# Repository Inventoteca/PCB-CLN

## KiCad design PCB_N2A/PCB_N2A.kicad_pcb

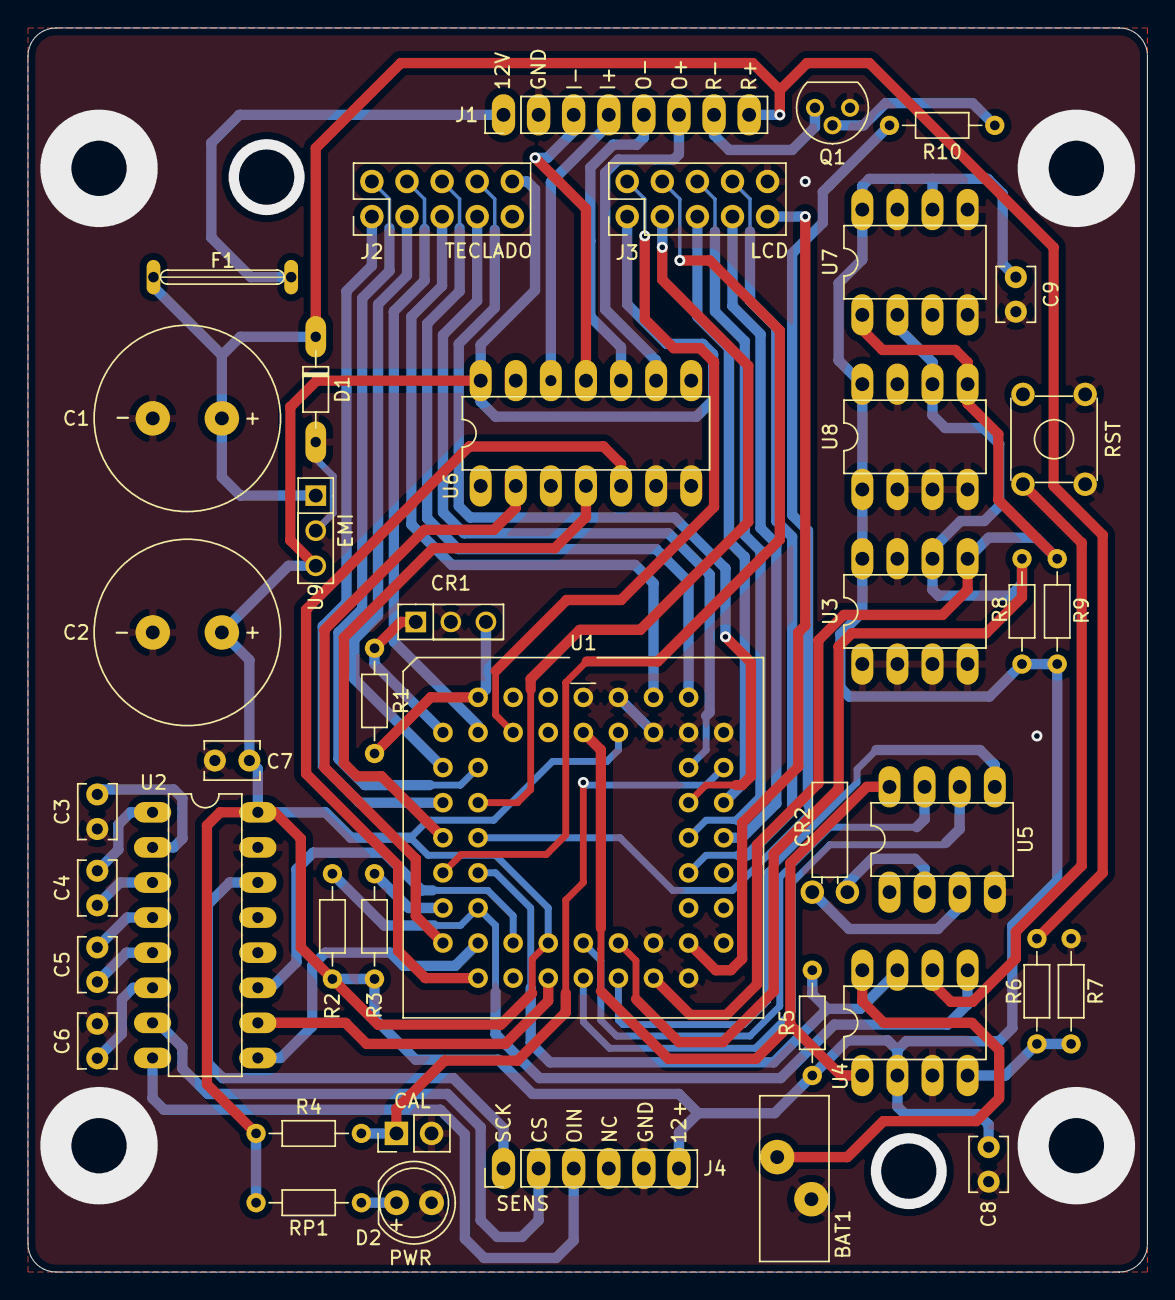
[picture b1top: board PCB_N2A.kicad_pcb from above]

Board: 2 copper layers, 81.0 x 90.0 mm, 42 parts (0 on the bottom side), 59 nets.

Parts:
BAT1: Battery_Cell; BatteryHolder_5.5_5mm
C1, C2: CP_Small; CP_13.25_5.0mm
C3, C4, C5, C6, C7, C8, C9: C_Small; C_Disc_D3.8mm_W2.6mm_P2.50mm
CAL: Conn_01x02; PinHeader_1x02_P2.54mm_Vertical
CR1: Crystal_GND2; Crystal_PIN-3
CR2: Crystal; crystal_2.54_8.7mm
D1: DIODE; D_DO-34_SOD68_P7.62mm_Horizontal
D2: RED; LED_D5.0mm_IRBlack
F1: Fuse; FUSE_10mm
J1: Conn_01x08; PinHeader_1x08_P2.54mm_Vertical
J2: Teclado; PinHeader_2x05_P2.54mm_Vertical
J3: LCD; PinHeader_2x05_P2.54mm_Vertical
J4: SENS; PinHeader_1x06_P2.54mm_Vertical
Q1: BC547; TO-92
R1: 10M; R_Axial_DIN0204_L3.6mm_D1.6mm_P7.62mm_Horizontal
R2, R3, R4, R5, R6, R8, R9, R10: 9.1k; R_Axial_DIN0204_L3.6mm_D1.6mm_P7.62mm_Horizontal
R7: 3.3k; R_Axial_DIN0204_L3.6mm_D1.6mm_P7.62mm_Horizontal
RP1: 360; R_Axial_DIN0204_L3.6mm_D1.6mm_P7.62mm_Horizontal
RST1: SW_Push_Dual; SW_TH_Tactile_Omron_B3F-10xx
U1: 68HC11_PLCC; PLCC-52_THT-Socket
U2: MAX232CPE; DIP-16_W7.62mm
U3, U8: 24LC65; DIP-8_W7.62mm
U4: MAX703; DIP-8_W7.62mm
U5: DS1302+; DIP-8_W7.62mm
U6: MAX491EPD; DIP-14_W7.62mm
U7: DS1621; DIP-8_W7.62mm
U9: EMI; Crystal_PIN-3

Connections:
Earth: BAT1.2, C1.2, C2.2, C3.1, C6.1, C7.2, C8.1, C9.2, CAL.2, CR1.2, D1.2, D2.2, J1.2, J3.10, J4.2, Q1.3, R7.2, RST1.1, RST1.2, U1.1, U1.3, U1.4, U1.32, U1.33, U1.34, U1.46, U1.48, U1.50, U1.51, U2.15, U3.1, U3.2, U3.3, U3.4, U3.7, U4.3, U5.4, U6.3, U6.6, U6.7, U7.4, U7.5, U7.7, U8.2, U8.3, U8.4, U8.7, U9.2
unnamed: BAT1.1, U4.8
unnamed: C1.1, D1.1, F1.1, J1.8, R6.1, U9.1
unnamed: C3.2, U2.2
unnamed: C4.1, U2.1
unnamed: C4.2, U2.3
unnamed: C5.1, U2.4
unnamed: C5.2, U2.5
unnamed: C6.2, U2.6
unnamed: CAL.1, R4.2, U1.44
unnamed: CR1.1, R1.1, U1.8
unnamed: CR1.3, R1.2, U1.7
unnamed: CR2.1, U5.2
unnamed: CR2.2, U5.3
unnamed: D2.1, RP1.2
unnamed: F1.2, J1.1
unnamed: J1.3, U6.11
unnamed: J1.4, U6.12
unnamed: J1.5, U6.10
unnamed: J1.6, U6.9
unnamed: J1.7, Q1.1
unnamed: J2.1, U1.12
unnamed: J2.2, U1.10
unnamed: J2.3, U1.49
unnamed: J2.4, U1.45
unnamed: J2.6, U1.11
unnamed: J2.7, U1.9
unnamed: J2.8, U1.47
unnamed: J2.9, U1.43
unnamed: J3.2, U1.13
unnamed: J3.3, U1.42
unnamed: J3.4, U1.40
unnamed: J3.5, U1.35
unnamed: J3.6, U1.6
unnamed: J3.7, U1.16
unnamed: J3.8, U1.41
unnamed: J3.9, U1.39
unnamed: J4.4, U2.8
unnamed: J4.5, U2.7
unnamed: J4.6, U2.14
unnamed: Q1.2, R10.1
unnamed: R2.2, U1.19, U4.5
unnamed: R3.2, U1.18
unnamed: R5.1, U1.17, U4.7
unnamed: R6.2, R7.1, U4.4
unnamed: R8.1, U1.30, U3.6, U7.2, U8.6
unnamed: R9.1, U1.31, U3.5, U7.1, U8.5
unnamed: R10.2, U1.15
unnamed: U1.2, U4.1, U5.8
unnamed: U1.14, U6.4
unnamed: U1.20, U6.2
unnamed: U1.21, U6.5
unnamed: U1.22, U2.9
unnamed: U1.24, U2.11
unnamed: U1.25, U2.10
unnamed: U1.27, U5.6
unnamed: U1.28, U5.7
unnamed: U1.29, U5.5
VDD: C2.1, C7.1, C8.2, C9.1, J2.10, J3.1, J4.1, R2.1, R3.1, R4.1, R5.2, R8.2, R9.2, RP1.1, U1.26, U1.52, U2.16, U3.8, U4.2, U6.14, U7.6, U7.8, U8.1, U8.8, U9.3

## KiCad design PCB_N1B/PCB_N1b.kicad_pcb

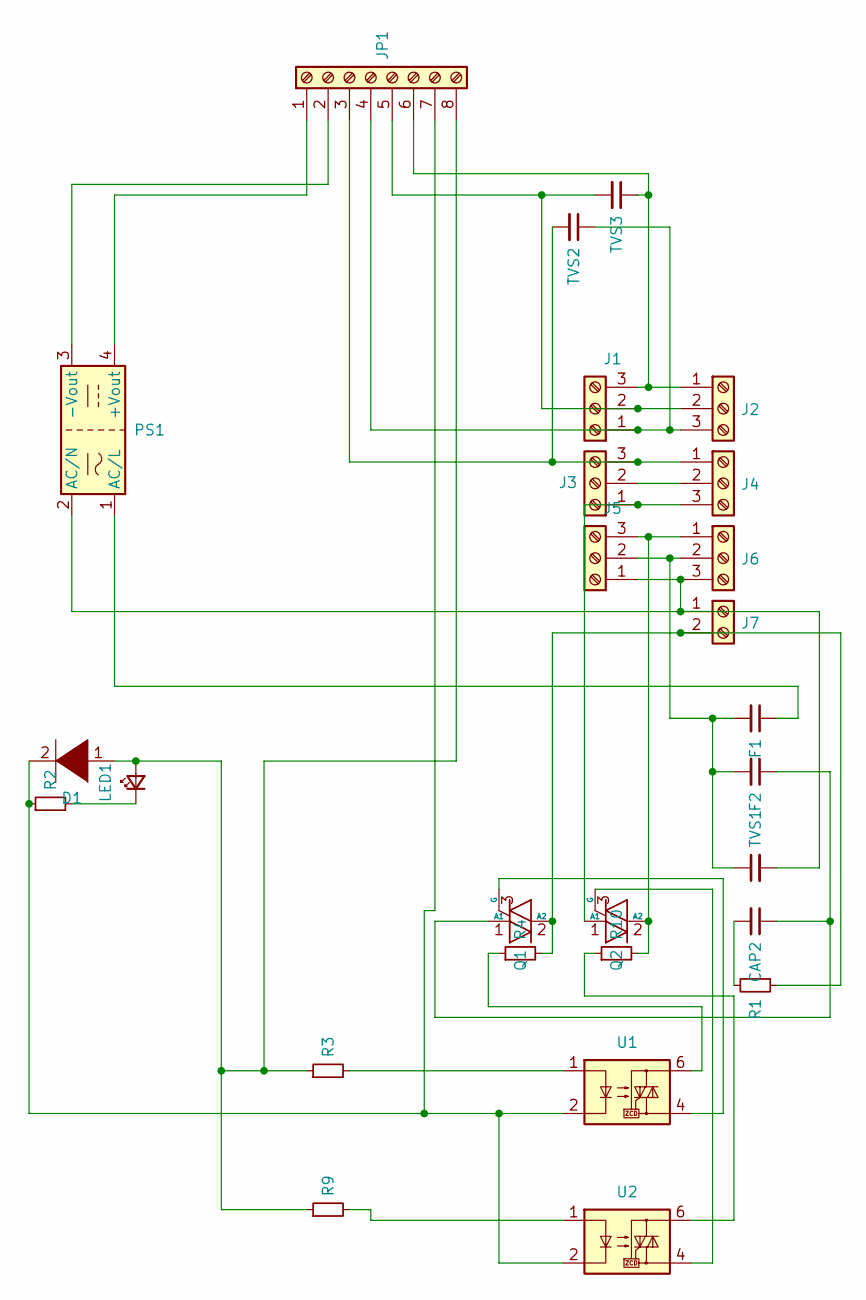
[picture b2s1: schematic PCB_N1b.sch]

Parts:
CAP2: 0.1uF 250V; C_Axial_L5.1mm_D3.1mm_P10.00mm_Horizontal
D1: na; D_DO-41_SOD81_P7.62mm_Horizontal
F1, F2: na; C_Axial_L5.1mm_D3.1mm_P10.00mm_Horizontal
J1, J2, J3, J4, J5, J6: Screw_Terminal_01x03; TerminalBlock_RND_205-00233_1x03_P5.08mm_Horizontal
J7: Screw_Terminal_01x02; TerminalBlock_RND_205-00232_1x02_P5.08mm_Horizontal
JP1: Screw_Terminal_01x08; PinHeader_1x08_P2.54mm_Vertical
LED1: red; LED_D3.0mm_Clear
PS1: HLK-PM01; Converter_ACDC_HiLink_HLK-PMxx
Q1, Q2: BTA08-600C; TO-220-3_Vertical
R1: na; R_Axial_DIN0207_L6.3mm_D2.5mm_P7.62mm_Horizontal
R2: 110; R_Axial_DIN0207_L6.3mm_D2.5mm_P7.62mm_Horizontal
R3, R4, R9, R10: 200; R_Axial_DIN0207_L6.3mm_D2.5mm_P7.62mm_Horizontal
TVS1: tf800; C_Axial_L5.1mm_D3.1mm_P10.00mm_Horizontal
TVS2, TVS3: na; C_Axial_L5.1mm_D3.1mm_P10.00mm_Horizontal
U1, U2: MOC3063; DIP-6_W7.62mm_LongPads

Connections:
unnamed: CAP2.1, F2.1, Q1.1 (A1)
unnamed: CAP2.2, R1.2
unnamed: D1.1 (K), JP1.8, LED1.2 (A), R3.1, R9.1
unnamed: D1.2 (A), JP1.7, R2.1, U1.2, U2.2
unnamed: F1.1, PS1.1 (AC/L)
unnamed: F1.2, F2.2, J5.2, J6.2, TVS1.1
unnamed: J1.1, J2.3, JP1.4, TVS2.1
unnamed: J1.2, J2.2, JP1.5, TVS3.2
unnamed: J1.3, J2.1, JP1.6, TVS3.1
unnamed: J3.1, J4.3, Q2.1 (A1)
unnamed: J3.2, J4.2
unnamed: J3.3, J4.1, JP1.3, TVS2.2
unnamed: J5.1, J6.3, J7.1, PS1.2 (AC/N), TVS1.2
unnamed: J5.3, J6.1, Q2.2 (A2), R10.2
unnamed: J7.2, Q1.2 (A2), R1.1, R4.2
unnamed: JP1.1, PS1.4 (+Vout)
unnamed: JP1.2, PS1.3 (-Vout)
unnamed: LED1.1 (K), R2.2
unnamed: Q1.3 (G), U1.4
unnamed: Q2.3 (G), U2.4
unnamed: R3.2, U1.1
unnamed: R4.1, U1.6
unnamed: R9.2, U2.1
unnamed: R10.1, U2.6

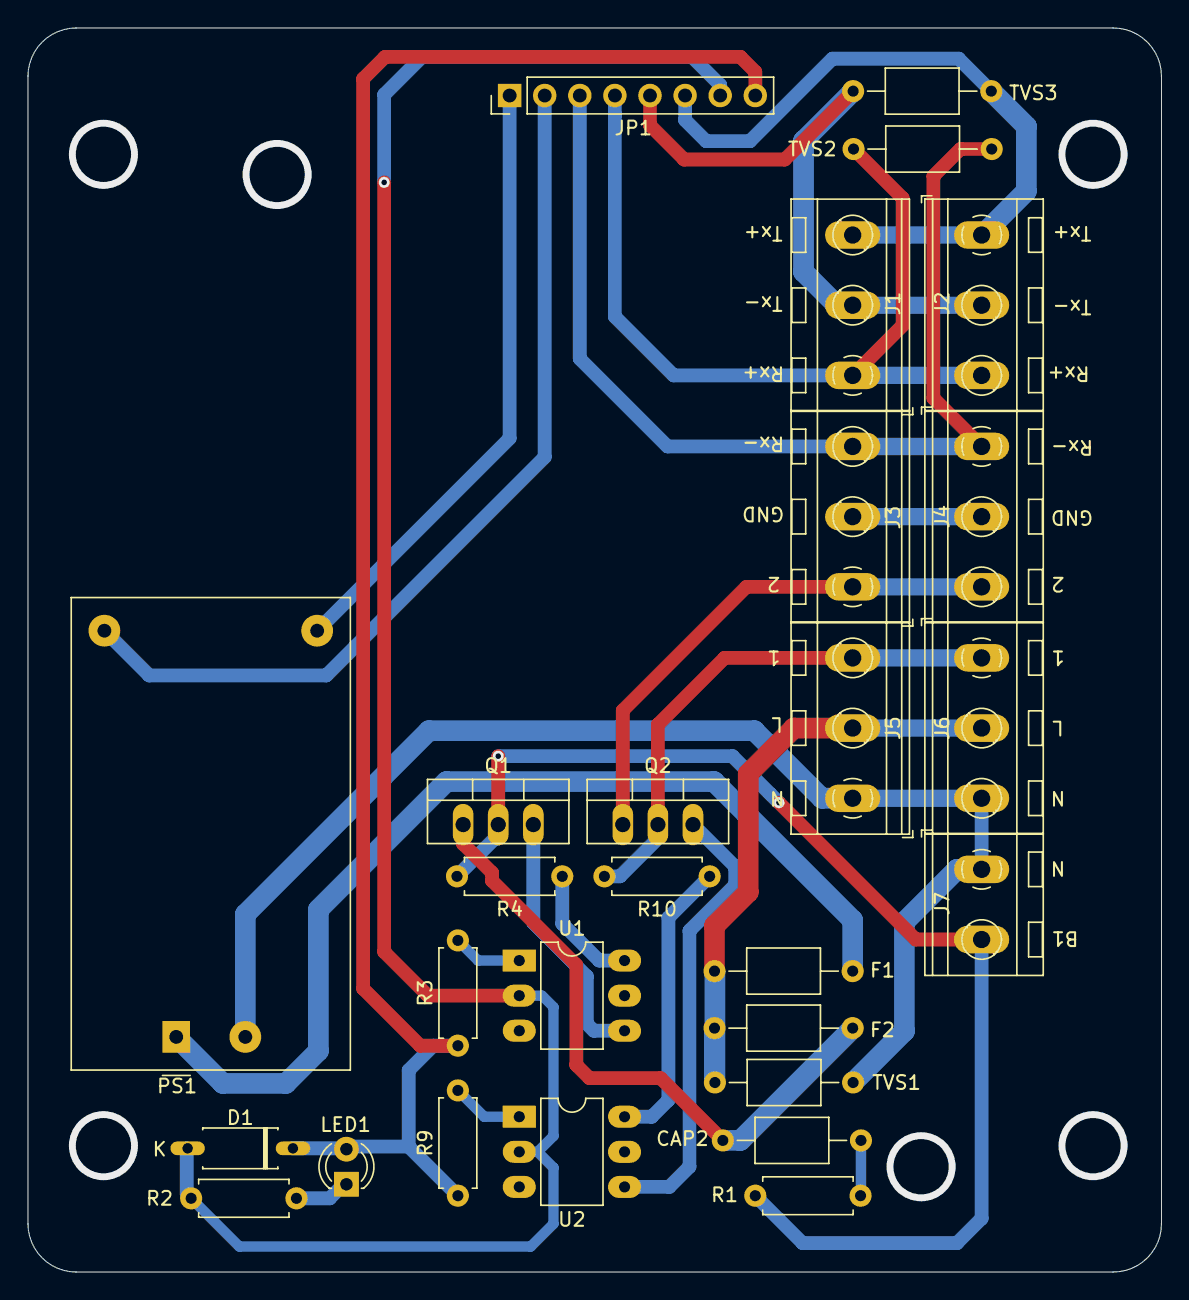
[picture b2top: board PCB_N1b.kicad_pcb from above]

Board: 2 copper layers, 82.0 x 90.0 mm, 27 parts (0 on the bottom side), 24 nets.

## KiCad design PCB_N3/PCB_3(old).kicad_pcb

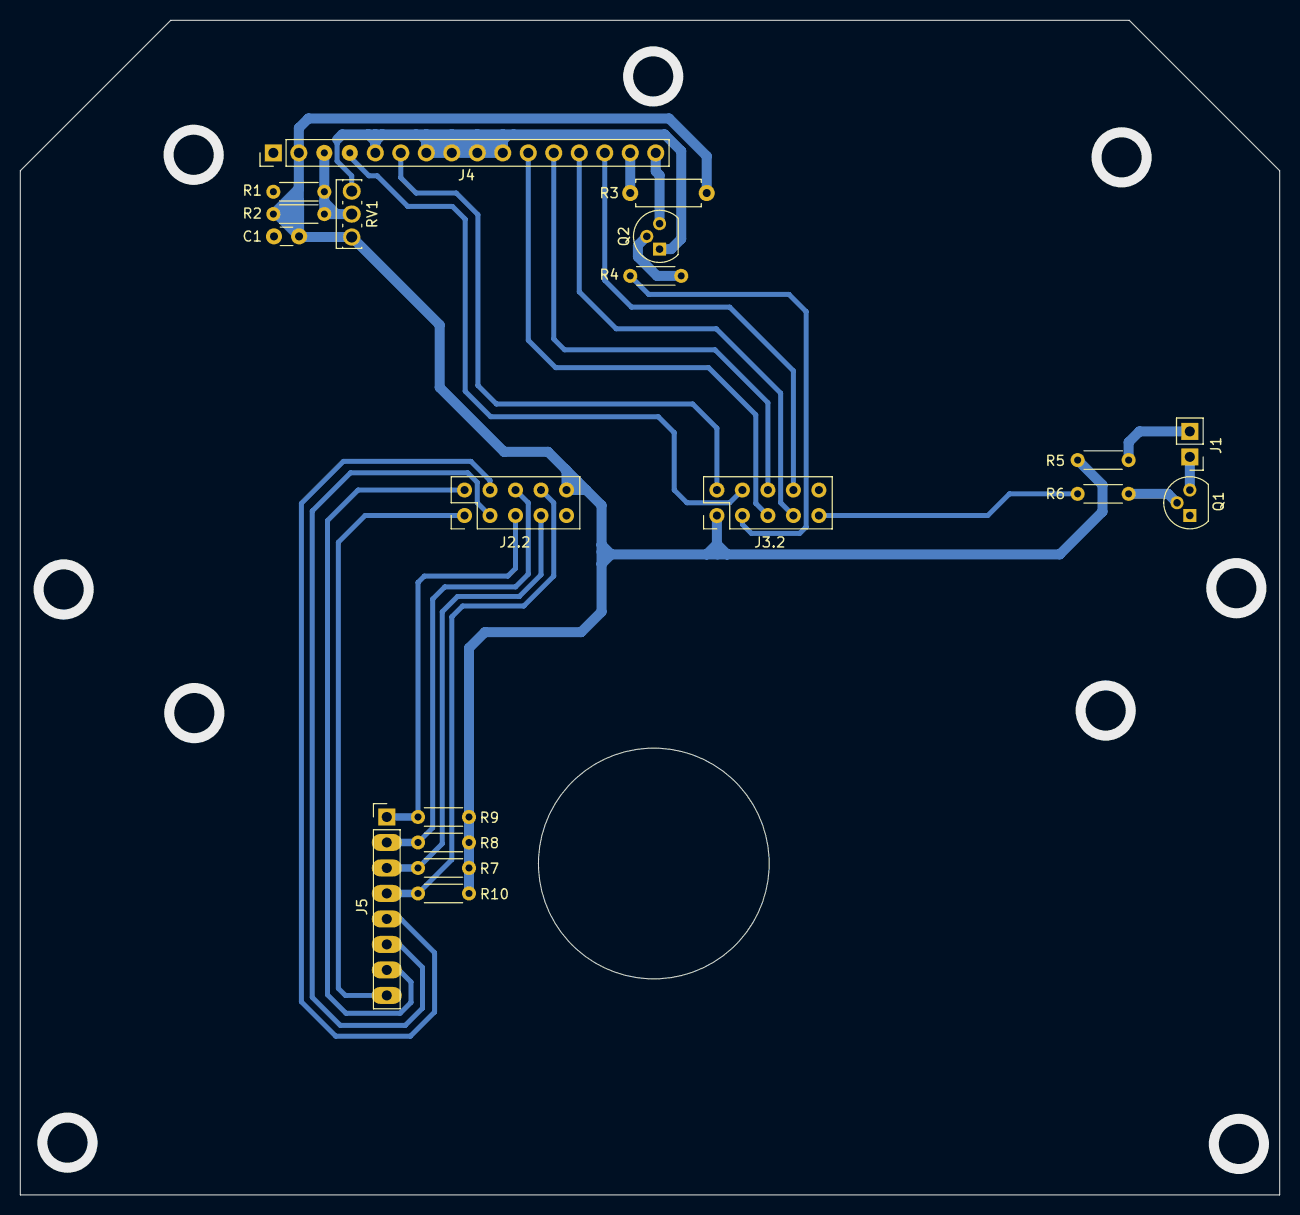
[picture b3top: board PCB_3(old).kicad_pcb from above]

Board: 2 copper layers, 125.5 x 117.0 mm, 19 parts (0 on the bottom side), 25 nets.

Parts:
C1: C_Small; C_Disc_D3.0mm_W1.6mm_P2.50mm
J1: Conn_01x02; PinHeader_1x02_P2.54mm_Vertical
J2.2, J3.2: Conn_02x05_Odd_Even; PinHeader_2x05_P2.54mm_Vertical
J4: Conn_01x16; PinHeader_1x16_P2.54mm_Vertical
J5: Conn_01x08; PinHeader_1x08_P2.54mm_Vertical
Q1, Q2: Q_NPN_EBC; TO-92
R1, R2, R4, R5, R6, R7, R8, R9, R10: R_Small; R_Axial_DIN0204_L3.6mm_D1.6mm_P5.08mm_Horizontal
R3: R_Small; R_Axial_DIN0207_L6.3mm_D2.5mm_P7.62mm_Horizontal
RV1: R_POT; SIPAK_Vertical

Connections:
Earth: C1.1, J3.2.10, J4.1, J4.5, J4.7, J4.8, J4.9, J4.10, Q1.1, Q2.1, R1.1, RV1.3
unnamed: C1.2, J2.2.10, J3.2.1, J4.2, R2.2, R3.1, R5.2, R7.1, R8.2, R9.2, R10.1, RV1.1
unnamed: J1.1, Q1.3
unnamed: J1.2, R5.1
unnamed: J2.2.1, J5.8
unnamed: J2.2.2, J5.7
unnamed: J2.2.3, J5.6
unnamed: J2.2.4, J5.5
unnamed: J2.2.5, J5.1, R9.1
unnamed: J2.2.6, J5.2, R8.1
unnamed: J2.2.7, J5.3, R7.2
unnamed: J2.2.8, J5.4, R10.2
unnamed: J3.2.2, J4.6
unnamed: J3.2.3, R4.1
unnamed: J3.2.4, J4.4
unnamed: J3.2.5, J4.11
unnamed: J3.2.6, J4.12
unnamed: J3.2.7, J4.13
unnamed: J3.2.8, J4.14
unnamed: J3.2.9, R6.2
unnamed: J4.3, R1.2, R2.1, RV1.2
unnamed: J4.15, R3.2
unnamed: J4.16, Q2.3
unnamed: Q1.2, R6.1
unnamed: Q2.2, R4.2

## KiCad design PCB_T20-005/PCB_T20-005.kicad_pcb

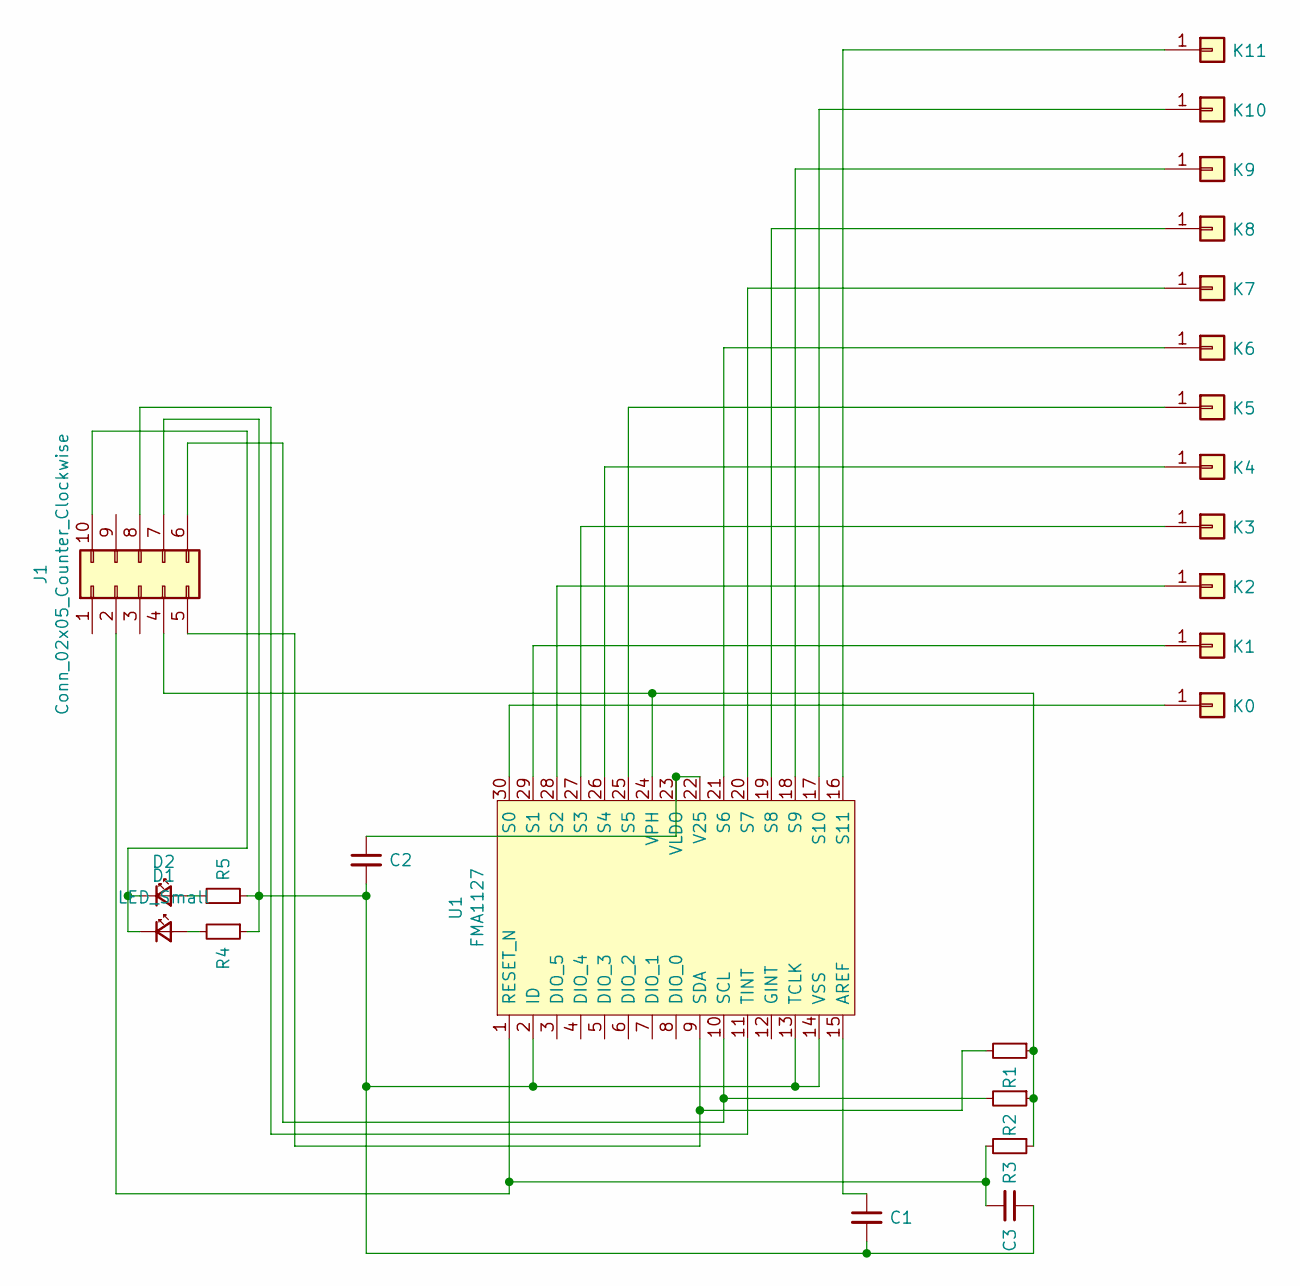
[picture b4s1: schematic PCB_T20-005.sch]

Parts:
C1, C2, C3: C_Small; C_0805_2012Metric
D1, D2: LED_Small; LED_Osram_Lx_P47F_D2mm_ReverseMount
J1: Conn_02x05_Counter_Clockwise; PinHeader_2x05_P2.54mm_Horizontal
K0, K1, K2, K3, K4, K5, K6, K7, K8, K9, K10, K11: Conn_01x01; kolas
R1, R2, R3: R_Small; R_0805_2012Metric
R4, R5: R_Small; R_1206_3216Metric
U1: FMA1127; SOIC-30

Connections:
unnamed: C1.1, U1.15 (AREF)
unnamed: C1.2, C2.2, C3.1, J1.7, R4.1, R5.2, U1.2 (ID), U1.13 (TCLK), U1.14 (VSS)
unnamed: C2.1, U1.22 (V25), U1.23 (VLDO)
unnamed: C3.2, J1.2, R3.2, U1.1 (RESET_N)
unnamed: D1.1 (K), D2.1 (K), J1.10
unnamed: D1.2 (A), R4.2
unnamed: D2.2 (A), R5.1
unnamed: J1.4, R1.1, R2.1, R3.1, U1.24 (VPH)
unnamed: J1.5, R1.2, U1.9 (SDA)
unnamed: J1.6, R2.2, U1.10 (SCL)
unnamed: J1.8, U1.11 (TINT)
unnamed: K0.1, U1.30 (S0)
unnamed: K1.1, U1.29 (S1)
unnamed: K2.1, U1.28 (S2)
unnamed: K3.1, U1.27 (S3)
unnamed: K4.1, U1.26 (S4)
unnamed: K5.1, U1.25 (S5)
unnamed: K6.1, U1.21 (S6)
unnamed: K7.1, U1.20 (S7)
unnamed: K8.1, U1.19 (S8)
unnamed: K9.1, U1.18 (S9)
unnamed: K10.1, U1.17 (S10)
unnamed: K11.1, U1.16 (S11)

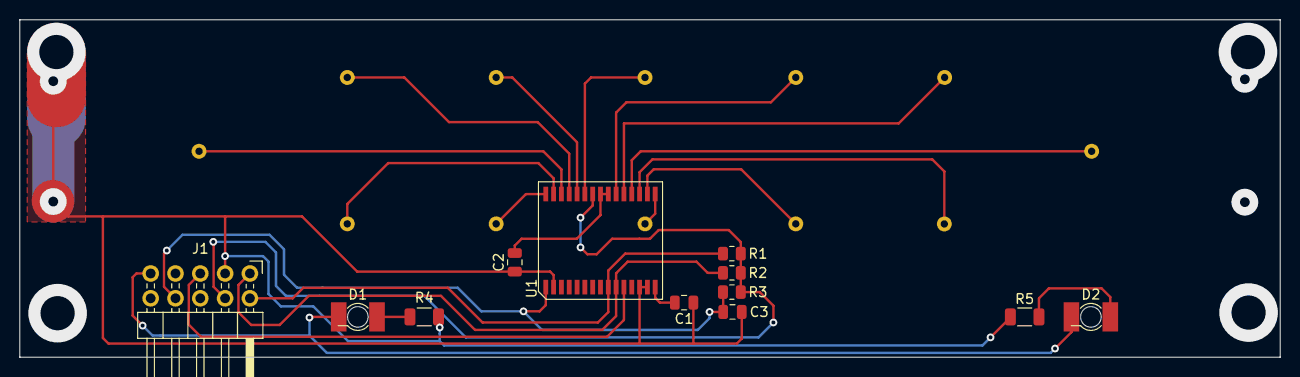
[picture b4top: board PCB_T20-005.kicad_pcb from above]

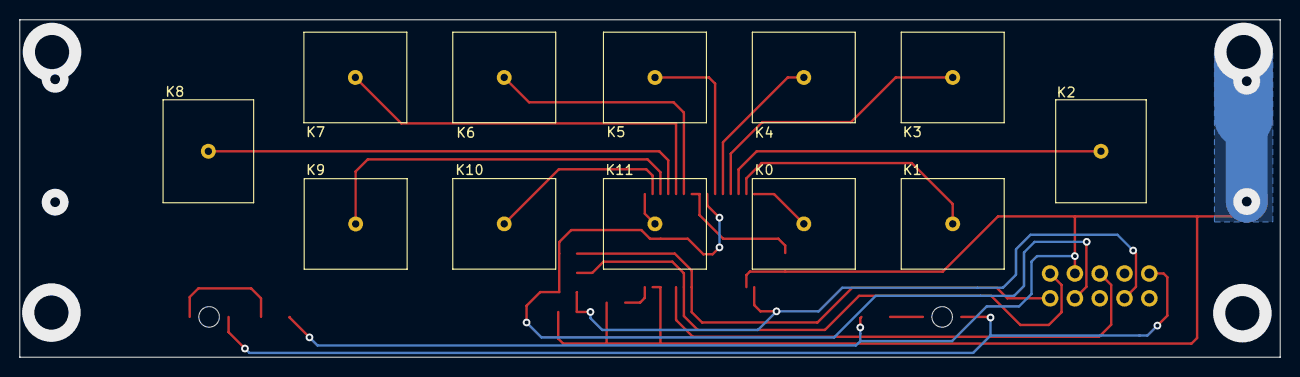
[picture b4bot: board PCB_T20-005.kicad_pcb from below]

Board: 2 copper layers, 129.0 x 34.5 mm, 24 parts (12 on the bottom side), 23 nets.

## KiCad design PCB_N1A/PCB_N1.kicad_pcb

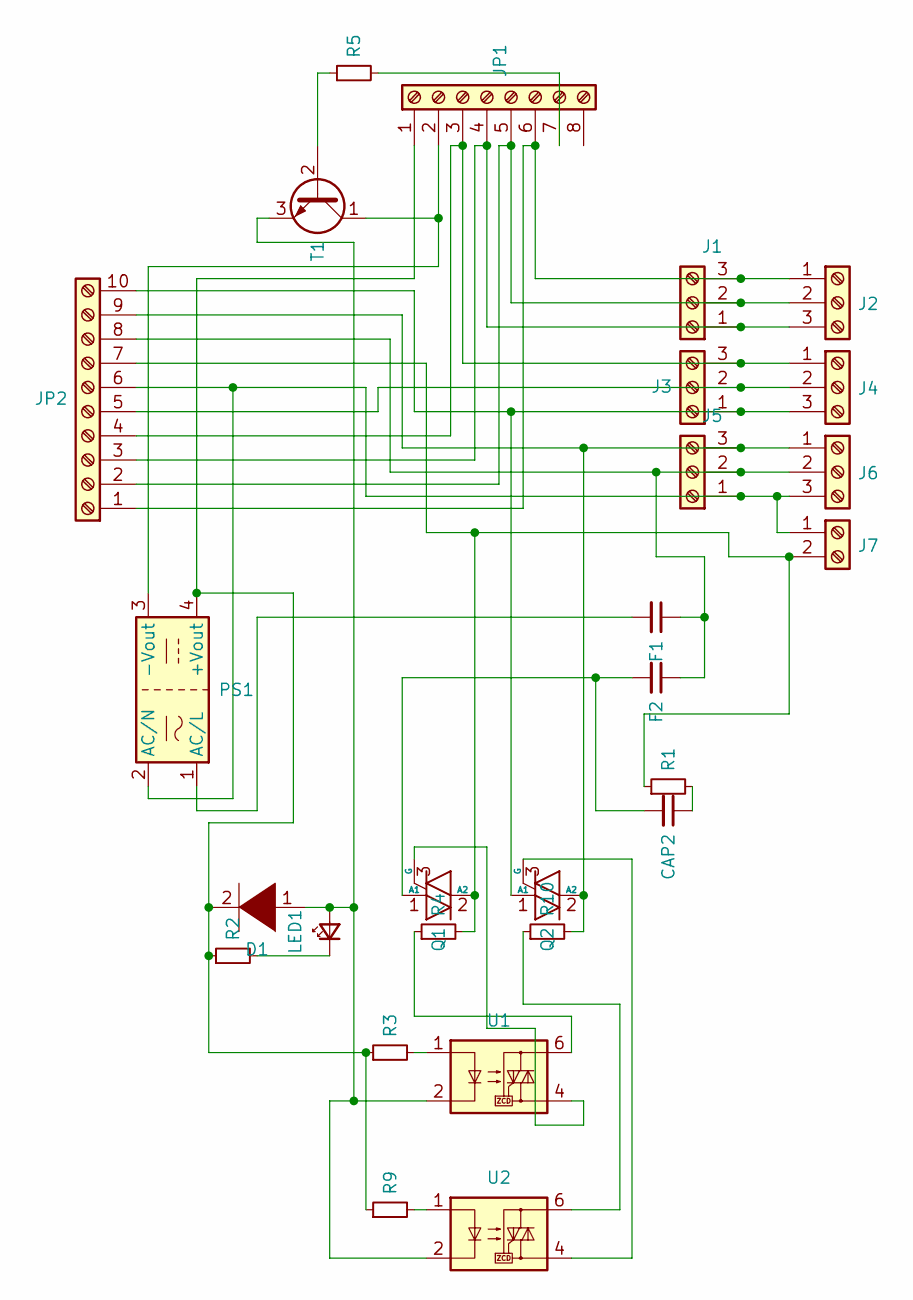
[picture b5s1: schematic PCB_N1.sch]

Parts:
CAP2: 0.1uF 400V; C_Axial_L5.1mm_D3.1mm_P10.00mm_Horizontal
D1: na; D_DO-41_SOD81_P7.62mm_Horizontal
F1, F2: na; C_Axial_L5.1mm_D3.1mm_P10.00mm_Horizontal
J1, J2, J3, J4, J5, J6: Screw_Terminal_01x03; TerminalBlock_RND_205-00233_1x03_P5.08mm_Horizontal
J7: Screw_Terminal_01x02; TerminalBlock_RND_205-00232_1x02_P5.08mm_Horizontal
JP1: Screw_Terminal_01x08; PinHeader_1x08_P2.54mm_Vertical
JP2: Screw_Terminal_01x10; PinHeader_1x10_P2.54mm_Horizontal
LED1: red; LED_D3.0mm_Clear
PS1: HLK-PM01; Converter_ACDC_HiLink_HLK-PMxx
Q1, Q2: BTA16-600B; TO-220-3_Vertical
R1: na; R_Axial_DIN0207_L6.3mm_D2.5mm_P7.62mm_Horizontal
R2: 110; R_Axial_DIN0207_L6.3mm_D2.5mm_P7.62mm_Horizontal
R3, R4, R9, R10: 200; R_Axial_DIN0207_L6.3mm_D2.5mm_P7.62mm_Horizontal
R5: 1k; R_Axial_DIN0207_L6.3mm_D2.5mm_P7.62mm_Horizontal
T1: BC547; TO-92_Inline
U1, U2: MOC3063; DIP-6_W7.62mm_LongPads

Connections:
unnamed: CAP2.1, R1.2
unnamed: CAP2.2, F2.2, Q1.1 (A1)
unnamed: D1.1 (K), LED1.2 (A), T1.3 (E), U1.2, U2.2
unnamed: D1.2 (A), JP1.1, PS1.4 (+Vout), R2.1, R3.1, R9.1
unnamed: F1.1, F2.1, J5.2, J6.2, JP2.8
unnamed: F1.2, PS1.1 (AC/L)
unnamed: J1.1, J2.3, JP1.4, JP2.3
unnamed: J1.2, J2.2, JP1.5, JP2.2
unnamed: J1.3, J2.1, JP1.6, JP2.1
unnamed: J3.1, J4.3, JP2.10, Q2.1 (A1)
unnamed: J3.2, J4.2, JP2.5
unnamed: J3.3, J4.1, JP1.3, JP2.4
unnamed: J5.1, J6.3, J7.1, JP2.6, PS1.2 (AC/N)
unnamed: J5.3, J6.1, JP2.9, Q2.2 (A2), R10.2
unnamed: J7.2, JP2.7, Q1.2 (A2), R1.1, R4.2
unnamed: JP1.2, PS1.3 (-Vout), T1.1 (C)
unnamed: JP1.7, R5.2
unnamed: LED1.1 (K), R2.2
unnamed: Q1.3 (G), U1.4
unnamed: Q2.3 (G), U2.4
unnamed: R3.2, U1.1
unnamed: R4.1, U1.6
unnamed: R5.1, T1.2 (B)
unnamed: R9.2, U2.1
unnamed: R10.1, U2.6

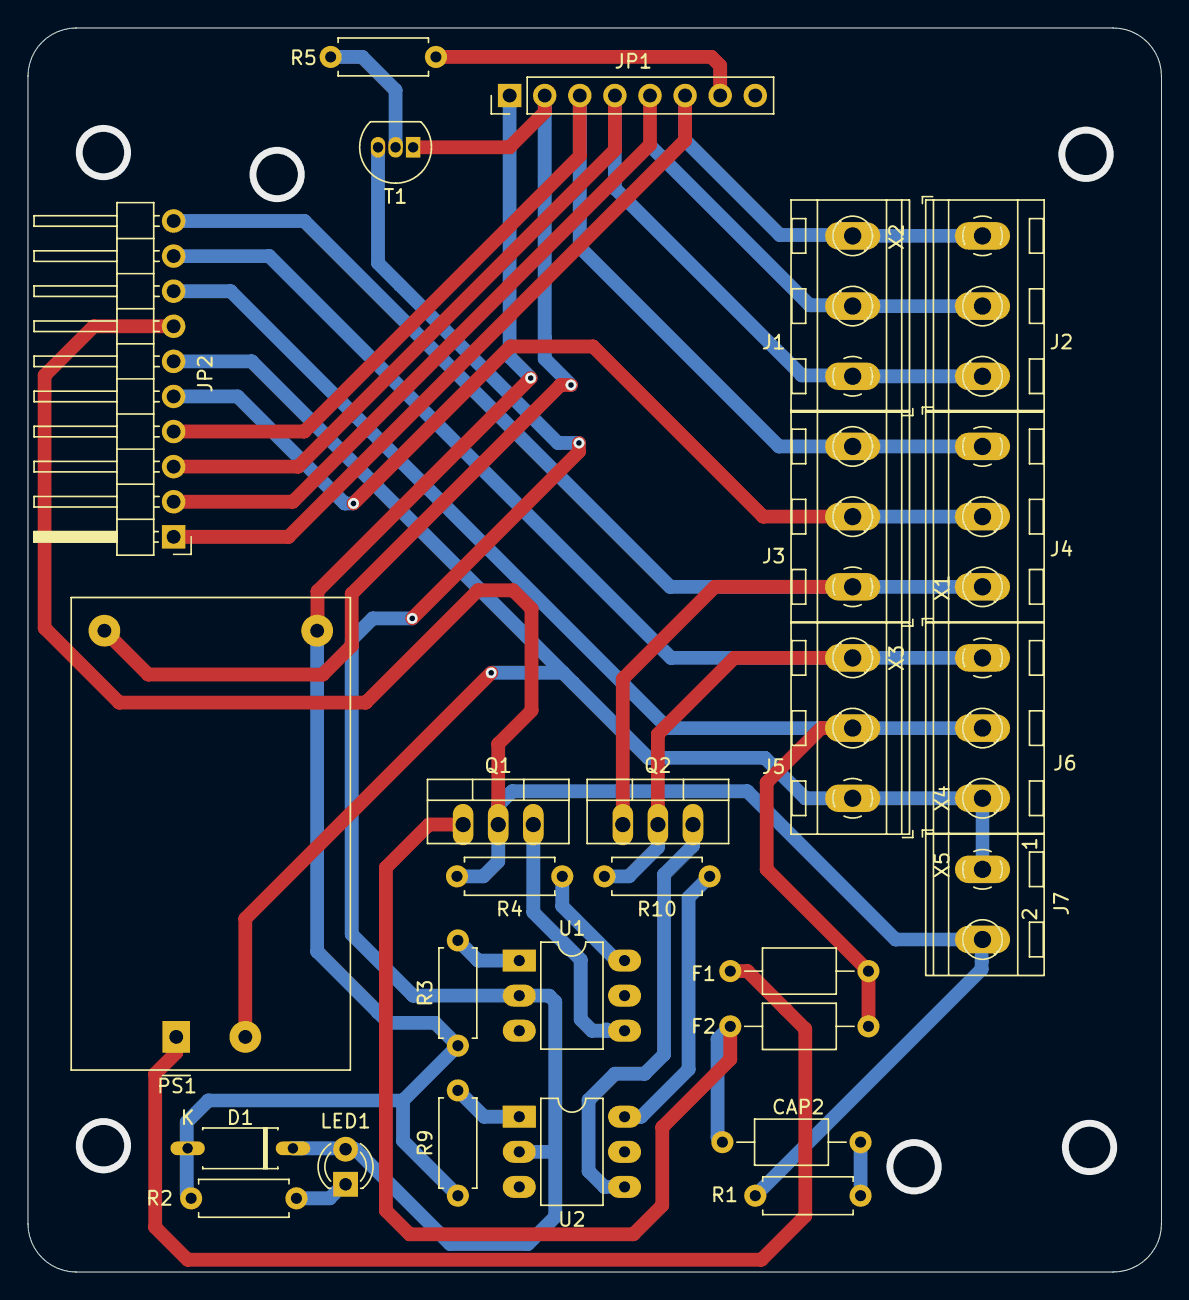
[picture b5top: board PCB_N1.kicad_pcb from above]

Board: 2 copper layers, 82.0 x 90.0 mm, 27 parts (0 on the bottom side), 25 nets.

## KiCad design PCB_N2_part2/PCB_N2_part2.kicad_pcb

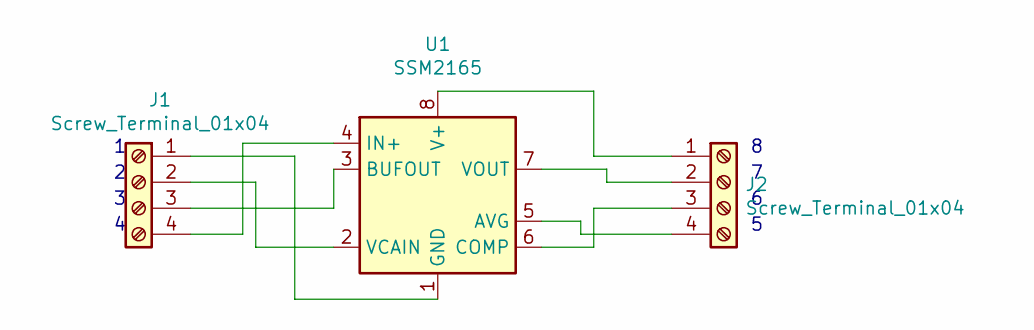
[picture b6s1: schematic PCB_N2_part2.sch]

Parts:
J1, J2: Screw_Terminal_01x04; PinSocket_1x04_P2.54mm_Vertical
U1: SSM2165; SO-8

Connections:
unnamed: J1.1, U1.1 (GND)
unnamed: J1.2, U1.2 (VCAIN)
unnamed: J1.3, U1.3 (BUFOUT)
unnamed: J1.4, U1.4 (IN+)
unnamed: J2.1, U1.8 (V+)
unnamed: J2.2, U1.7 (VOUT)
unnamed: J2.3, U1.6 (COMP)
unnamed: J2.4, U1.5 (AVG)

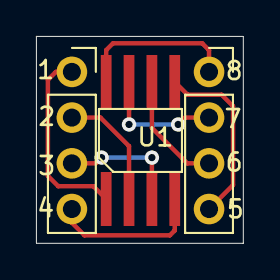
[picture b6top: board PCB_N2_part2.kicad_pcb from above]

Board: 2 copper layers, 11.5 x 11.5 mm, 3 parts (0 on the bottom side), 8 nets.

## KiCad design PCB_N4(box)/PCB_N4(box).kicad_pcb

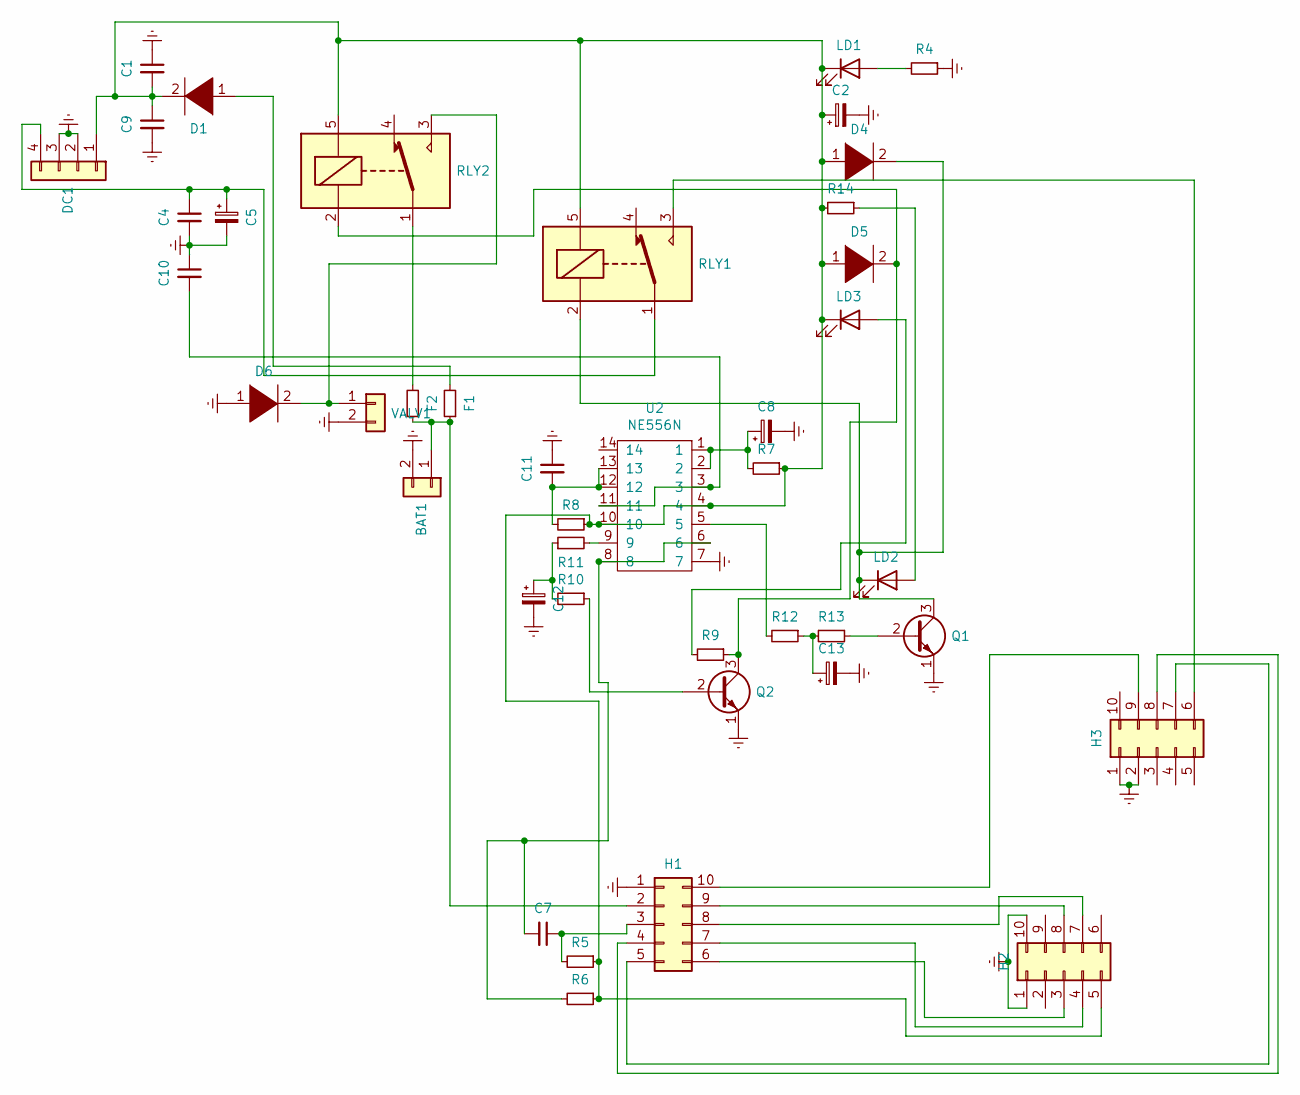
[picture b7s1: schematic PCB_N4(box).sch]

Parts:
BAT1: Conn_01x02; TerminalBlock_bornier-2_P5.08mm
C1, C4, C7, C9, C10, C11: C_Small; C_Rect_L7.0mm_W2.5mm_P5.00mm
C2, C5: CP_Small; C_Radial_D12.5mm_H20.0mm_P5.00mm
C8: CP_Small; CP_Radial_Tantal_D10.5mm_P2.50mm
C12: CP_Small; CP_Radial_D6.3mm_P2.50mm
C13: CP_Small; CP_Radial_D10.0mm_P3.80mm
D1: DIODE; diod_10-15.24mm
D4, D5, D6: DIODE; diod_2.54-10.16
DC1: Conn_01x04; PinHeader_1x04_P2.54mm_Horizontal
F1, F2: R_Small; fuse_7.62mm
H1, H2, H3: Conn_02x05_Counter_Clockwise; PinHeader_2x05_P2.54mm_Vertical
LD1, LD2, LD3: LED; LED_D3.0mm
Q1, Q2: PN2222A; TO-92
R4, R5, R6, R7, R8, R9, R10, R11, R12, R13, R14: R_Small; R_Axial_DIN0207_L6.3mm_D2.5mm_P7.62mm_Horizontal
RLY1, RLY2: SANYOU_SRD_Form_C; Relay_SPDT_SANYOU_SRD_Series_Form_C
U2: NE556N; DIP-14_W7.62mm
VALV1: Conn_01x02; TerminalBlock_bornier-2_P5.08mm

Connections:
Earth: BAT1.2, C1.1, C2.2, C4.2, C5.2, C8.2, C9.2, C10.1, C11.1, C12.2, C13.2, D6.1 (K), DC1.2, DC1.3, H1.1, H2.1, H2.10, H3.1, H3.2, Q1.1 (E), Q2.1 (E), R4.1, U2.7, VALV1.2
unnamed: BAT1.1, F1.1, F2.1, H1.2
unnamed: C1.2, C2.1, C9.1, D1.2 (A), D4.1 (K), D5.1 (K), DC1.1, H2.5, LD1.1 (K), LD3.1 (K), R5.1, R6.1, R7.1, R8.1, R14.2, RLY1.5, RLY2.5, U2.4, U2.10
unnamed: C4.1, C5.1, DC1.4, RLY1.1
unnamed: C7.1, H1.3, R5.2
unnamed: C7.2, R6.2, U2.6, U2.8
unnamed: C8.1, R7.2, U2.1, U2.2
unnamed: C10.2, U2.3, U2.11
unnamed: C11.2, R8.2, U2.12, U2.13
unnamed: C12.1, R10.2, R11.1
unnamed: C13.1, R12.1, R13.2
unnamed: D1.1 (K), F1.2
unnamed: D4.2 (A), LD2.1 (K), Q1.3 (C), RLY1.2
unnamed: D5.2 (A), Q2.3 (C), R9.1, RLY2.2
unnamed: D6.2 (A), RLY2.3, VALV1.1
unnamed: F2.2, RLY2.1
unnamed: H1.4, H3.8
unnamed: H1.5, H3.7
unnamed: H1.6, H2.3
unnamed: H1.7, H2.4
unnamed: H1.8, H2.7
unnamed: H1.9, H2.8
unnamed: H1.10, H3.9
unnamed: H3.6, RLY1.3
unnamed: LD1.2 (A), R4.2
unnamed: LD2.2 (A), R14.1
unnamed: LD3.2 (A), R9.2
unnamed: Q1.2 (B), R13.1
unnamed: Q2.2 (B), R10.1
unnamed: R11.2, U2.9
unnamed: R12.2, U2.5

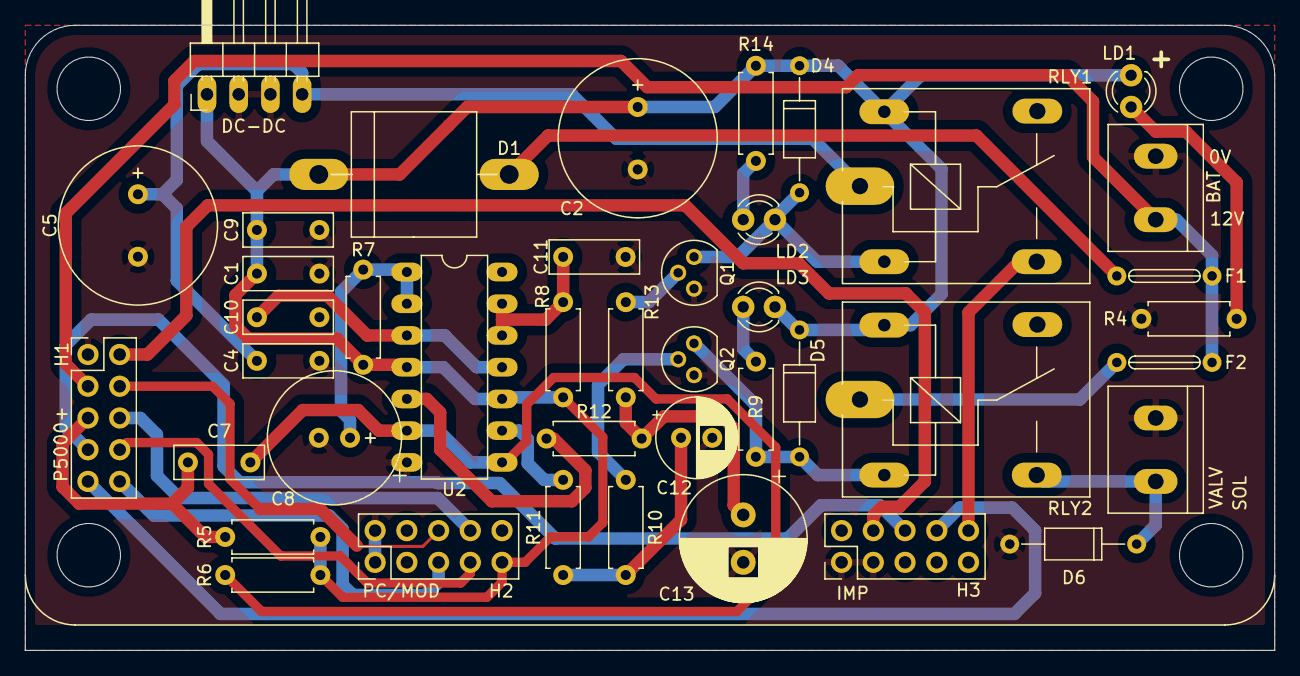
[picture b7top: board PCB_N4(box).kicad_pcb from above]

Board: 2 copper layers, 100.0 x 50.0 mm, 42 parts (0 on the bottom side), 31 nets.
